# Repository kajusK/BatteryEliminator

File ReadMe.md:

# Battery eliminator for NavComm NC-55A

The aim of this project is to eliminate battery from the [NavComm NC-55A airband](https://navcomm.eu/en/air-band/15-handheld-air-band-radio-with-vor-and-bluetooth-5907662381407.html#/wersje_nc_55a-basic/battery_type-battery_li_po_2400mah)
radio by providing a regulated voltage supply directly through the battery
contacts of the radio.

## Design constraints

- Radio uses 2 cell Li-Ion battery used -> 7.4 V nominal working voltage
- Radio current consumption: 1 A for Tx, 70 mA for Rx per manual
- Input voltage range 8-28 V of aircraft power bus (12 V nominal)
- Good input voltage noise filtering is needed - spikes on engine startup, etc.

## Mechanical design

- The mechanical part (holder) of the project was designed in a way that it can be clicked to the radio back in similar way as the battery
- The holder serves as a battery replacement and in the same time as a mounting point of the radio to the aircraft panel
- A simple connector to accomodate 2 jacks needed by the radio (mic, headphones, PTT) is included in the design files
- Design files can be found in [3d folder](./3d) or on my [Onshape profile](https://cad.onshape.com/documents/5d88d10385b6e47e38e9babd/w/7460efe50eb1ed31b91b954c/e/4510368ee41f3908bf5426d3?renderMode=0&uiState=67194a155a797301722a329e)

## PCB Design

### Input protection

- Polarity protection using **SBR3U40S1F** diode
- Transient protections using **SMDJ28CA** 28V 3kW TVS diode
- Shorts protection using a fuse - assuming 1 A output and 80 % efficiency at minimum working voltage, 1.3 A hold current at 80°C is needed. The **C1Q 1.25** will be used.

### Input filtering

A simple SMD ferrite bead followed by 100 nF and Buck converter input capacitors
provides input filtering to reduce amount of noise going from the DC/DC supply
to the aircraft power bus.

### DC-DC converter

As the voltage difference is quite high (worst case 28 - 7.4 = 20.6 V / 1 A
output), the LDO is not a good choice here, switching supply is needed.

- Buck topology
- ~8-30+ V input voltage range
- more than 1 A output current
- Large output current range (light load mode is possible)

The **AP63200WU-7** was selected as it matches all requirements and
requires a minimum amount of external parts.

- 2 A output current limit
- 3.8 - 32 V input voltage
- 500 kHz switching frequency with spread spectrum to reduce EMI
- integrated MOSFETs
- PFM mode for high efficiency on low output currents
- Overvoltage and overtemperature protection

The feedback voltage reference is 0.8 V, a 75k and 9k1 5% resistors will be used,
giving output voltage (worst case) between 6.77 and 8.09 V which is well within
input voltage range of the radio, a 1 % resistors would be better though.

The inductor will be (assuming 50 % ripple current of 2 A - 1 A):

$$ L = \frac{V_{out}(V_{in}-V_{out})}{V_{in}\Delta I_L f_{sw}} = \frac{7.4 (28-7.4)}{28*1*500000} = 10.9 \mu H $$

The datasheet recommended maximum inductance od 10 $$\mu H$$, so let's stick with
this. The recommended RDC is 100 $m\Omega$ and saturation current 35 % higher than peak one.
The **SRR6028-100Y** was selected.

### Output filtering

Output is fed through a ferrite bead to a parallel combination of small ceramic
capacitor and a large capacitor with higher ESR to provide some dumping.

### Output protection

The output of the switching regulator is separated from radio by a fuse
and a TVS diode to protect the circuit from ESD when radio is not connected.

## Testing

- Measured at 13 V input voltage (usual value when engine is running in 12 V based aircraft power system)
- Radio consumption pulses between 20 and 44 mA in Rx while battery saving is enabled, the coil makes annoying buzzing noise
- With battery saving off -> 44 mA constant current, the coil makes very weak high pitch sound
- With backlight on, consumption is 90 mA, no audible noise from coil
- When transmitting, the consumption is around 700 mA

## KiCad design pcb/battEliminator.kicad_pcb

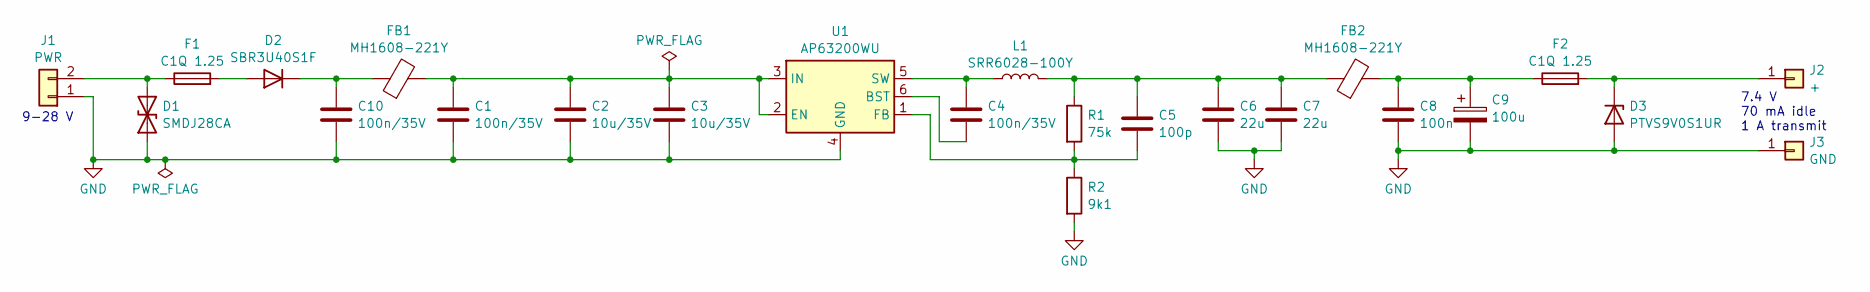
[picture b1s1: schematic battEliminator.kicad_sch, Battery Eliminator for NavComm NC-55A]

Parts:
C1, C4, C10: 100n/35V; C_0603_1608Metric
C2, C3: 10u/35V; C_1206_3216Metric; Mouser number 187-CL31B106KBHNNNE
C5: 100p; C_0603_1608Metric; Mouser number 80-C0603C101J1G
C6, C7: 22u; C_0805_2012Metric; Mouser number 81-GRM21BR61E226ME4L
C8: 100n; C_0603_1608Metric
C9: 100u; CP_EIA-7343-30_AVX-N; Mouser number 581-TAJD107M016R
D1: SMDJ28CA; D_SMC; Mouser number 576-SMDJ28CA
D2: SBR3U40S1F; D_SOD-123F; Mouser number 621-SBR3U40S1F-7
D3: PTVS9V0S1UR; D_SOD-123
F1, F2: C1Q 1.25; Fuse_1206_3216Metric; Mouser number 530-C1Q1.25
FB1, FB2: MH1608-221Y; L_0603_1608Metric; Mouser number 652-MH1608-221Y
J1: PWR; PhoenixContact_MCV_1,5_2-G-3.81_1x02_P3.81mm_Vertical
J2: +; TestPoint_Pad_D3.0mm
J3: GND; TestPoint_Pad_D3.0mm
L1: SRR6028-100Y; L_Cenker_CKCS8040; Mouser number 652-SRR6028-100Y
R1: 75k; R_0603_1608Metric
R2: 9k1; R_0603_1608Metric
U1: AP63200WU; TSOT-23-6; Mouser number 621-AP63200WU-7

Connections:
GND: C1.2, C2.2, C3.2, C6.2, C7.2, C8.2, C9.2, C10.2, D1.1 (A1), D3.2 (A), J1.1, J3.1, R2.2, U1.4 (GND)
unnamed: C5.1, C6.1, C7.1, FB2.1, L1.2, R1.1
unnamed: C8.1, C9.1, F2.1, FB2.2
unnamed: D1.2 (A2), F1.1, J1.2
unnamed: D2.2 (A), F1.2
unnamed: C10.1, D2.1 (K), FB1.1
unnamed: D3.1 (K), F2.2, J2.1
unnamed: C4.1, U1.6 (BST)
unnamed: C1.1, C2.1, C3.1, FB1.2, U1.2 (EN), U1.3 (IN)
unnamed: C5.2, R1.2, R2.1, U1.1 (FB)
unnamed: C4.2, L1.1, U1.5 (SW)

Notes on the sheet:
9-28 V
7.4 V 70 mA idle 1 A transmit

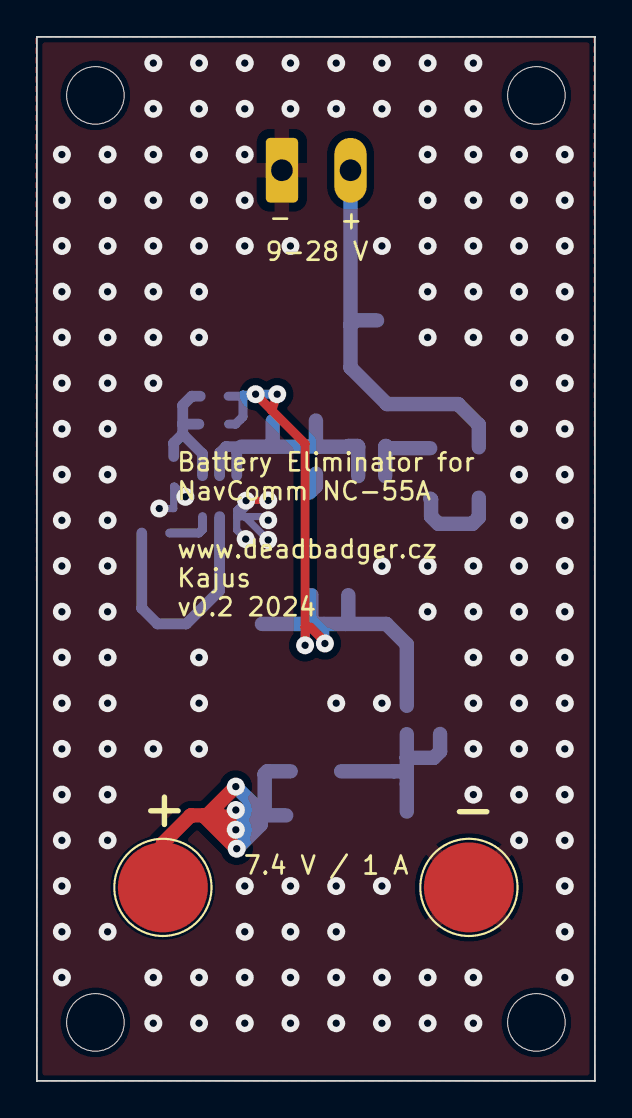
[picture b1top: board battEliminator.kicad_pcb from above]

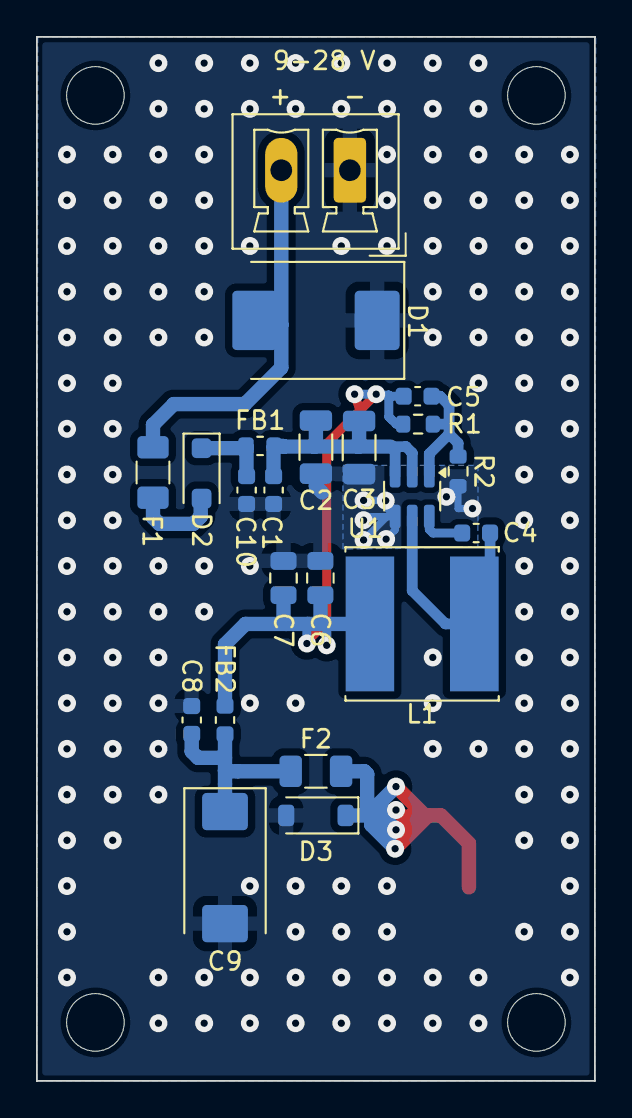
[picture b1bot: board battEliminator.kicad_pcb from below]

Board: 2 copper layers, 31.0 x 58.0 mm, 24 parts (22 on the bottom side), 11 nets.

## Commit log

2024-08-26 Added readme and PCB design
2024-08-26 Added gerber files for PCB
2024-10-23 Updated readme with testing results
2024-10-23 Fixed size and position of the radio battery pads
2024-10-23 Regenerated gerbers for pcb v0.2
2024-10-23 Added remaining design files and image
